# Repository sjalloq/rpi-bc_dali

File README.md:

# rpi-bc_dali
A Dali expander board for the [Phoenix RPI-BC](https://www.phoenixcontact.com/online/portal/gb/pxc/product_list_pages/!ut/p/z1/xVRdb9sgFP0te_AjBscUk72lUZWoq6V13daYF4svO7QxUIfEzb8f3ipVm9ZEUxWNB7hI5557zxEXyOAKMsv3puXBOMs38V4xUtPJp_lygbOSXt1M0G1Z3izxl6zIZgh-hwwyL42CVUNy3WCFAZ5iATClHAhFCWikmnB8UVCJ8xEtbfBhDatWaJugQYsEddzE0PdO7WTYJmhjtqH2vNUxVnqvN8532ob60YS69wYIWXuAMpBNxh0VCeIFVWQqc1Ag0gCMCAdTRXKAeKMKnskpQgLeH1WzwJAdF_srH72xIuBEfhXzizcBtxje740e4Dfr-i6af_eP3i5PViDvrHCC_uKs9OS89OV5zSmLs9Jfvbf761OPN34F5uHpic3iBDsb9HOAq_8xwuxoo-MQ_wQcmdI7bevFZf15NV9cjrqN6NJBdilK_bNMXyTUrwJG6TMrctpC1utG97pPd338HNch-O3HBEULhiFtnWs3OpUu3T0m6G9Ja7eNpv2Jhb7raH4woLreD8PXppsL-vtxyNEDZuIwzD78AHHaYK8!/?q=rpi-bc&uri=pxc-search%3Awebsite&library=gben) case.

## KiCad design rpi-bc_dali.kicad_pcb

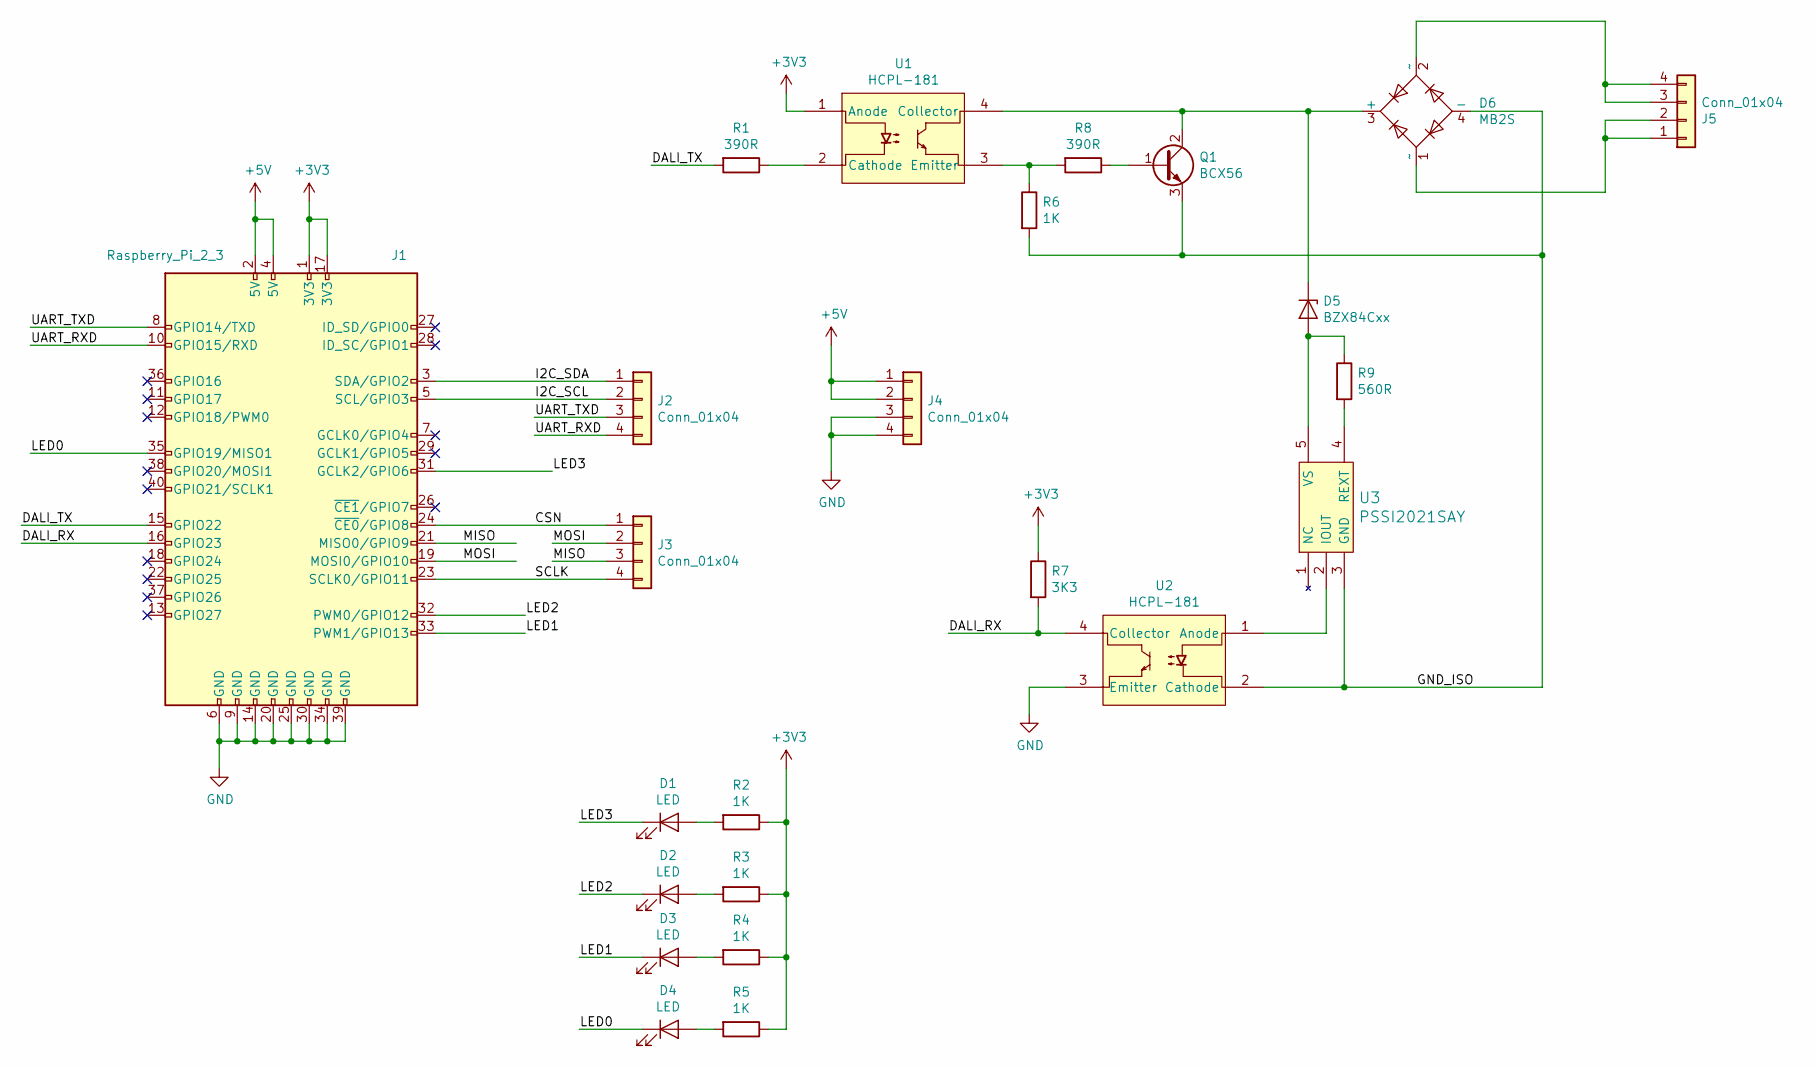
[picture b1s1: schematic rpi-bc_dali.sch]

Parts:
D1, D2, D3, D4: LED; LED_0603_1608Metric_Pad1.05x0.95mm_HandSolder
D5: BZX84Cxx; D_SOT-23_ANK
D6: MB2S; TO-269AA
J1: Raspberry_Pi_2_3; PinSocket_2x20_P2.54mm_Vertical
J2, J3, J4, J5: Conn_01x04; TerminalBlock_Phoenix_PTSM-0,5-4-HH-2,5-THR_1x04_P2.50mm_Ho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
Q1: BCX56; SOT-89-3
R1, R8: 390R; R_0603_1608Metric_Pad1.05x0.95mm_HandSolder
R2, R3, R4, R5, R6: 1K; R_0603_1608Metric_Pad1.05x0.95mm_HandSolder
R7: 3K3; R_0603_1608Metric_Pad1.05x0.95mm_HandSolder
R9: 560R; R_0603_1608Metric_Pad1.05x0.95mm_HandSolder
U1, U2: HCPL-181; SO-4_4.4x3.6mm_P2.54mm
U3: PSSI2021SAY; SOT-353_SC-70-5_Handsoldering

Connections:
+3V3: J1.1 (3V3), J1.17 (3V3), R2.1, R3.1, R4.1, R5.1, R7.1, U1.1 (Anode)
+5V: J1.2 (5V), J1.4 (5V), J4.1, J4.2
/CSN: J1.24 (~CE0~/GPIO8), J3.1
/DALI_RX: J1.16 (GPIO23), R7.2, U2.4 (Collector)
/DALI_TX: J1.15 (GPIO22), R1.2
/GND_ISO: D6.4 (-), Q1.3 (E), R6.2, U2.2 (Cathode), U3.3 (GND)
/I2C_SCL: J1.5 (SCL/GPIO3), J2.2
/I2C_SDA: J1.3 (SDA/GPIO2), J2.1
/LED0: D4.1 (K), J1.35 (GPIO19/MISO1)
/LED1: D3.1 (K), J1.33 (PWM1/GPIO13)
/LED2: D2.1 (K), J1.32 (PWM0/GPIO12)
/LED3: D1.1 (K), J1.31 (GCLK2/GPIO6)
/MISO: J1.21 (MISO0/GPIO9), J3.3
/MOSI: J1.19 (MOSI0/GPIO10), J3.2
/SCLK: J1.23 (SCLK0/GPIO11), J3.4
/UART_RXD: J1.10 (GPIO15/RXD), J2.4
/UART_TXD: J1.8 (GPIO14/TXD), J2.3
GND: J1.6 (GND), J1.9 (GND), J1.14 (GND), J1.20 (GND), J1.25 (GND), J1.30 (GND), J1.34 (GND), J1.39 (GND), J4.3, J4.4, U2.3 (Emitter)
unnamed: D1.2 (A), R2.2
unnamed: D2.2 (A), R3.2
unnamed: D3.2 (A), R4.2
unnamed: D4.2 (A), R5.2
unnamed: D5.1 (K), D6.3 (+), Q1.2 (C), U1.4 (Collector)
unnamed: D5.2 (A), R9.1, U3.5 (VS)
unnamed: D6.1 (~~), J5.1, J5.2
unnamed: D6.2 (~~), J5.3, J5.4
unnamed: Q1.1 (B), R8.1
unnamed: R1.1, U1.2 (Cathode)
unnamed: R6.1, R8.2, U1.3 (Emitter)
unnamed: R9.2, U3.4 (REXT)
unnamed: U2.1 (Anode), U3.2 (IOUT)

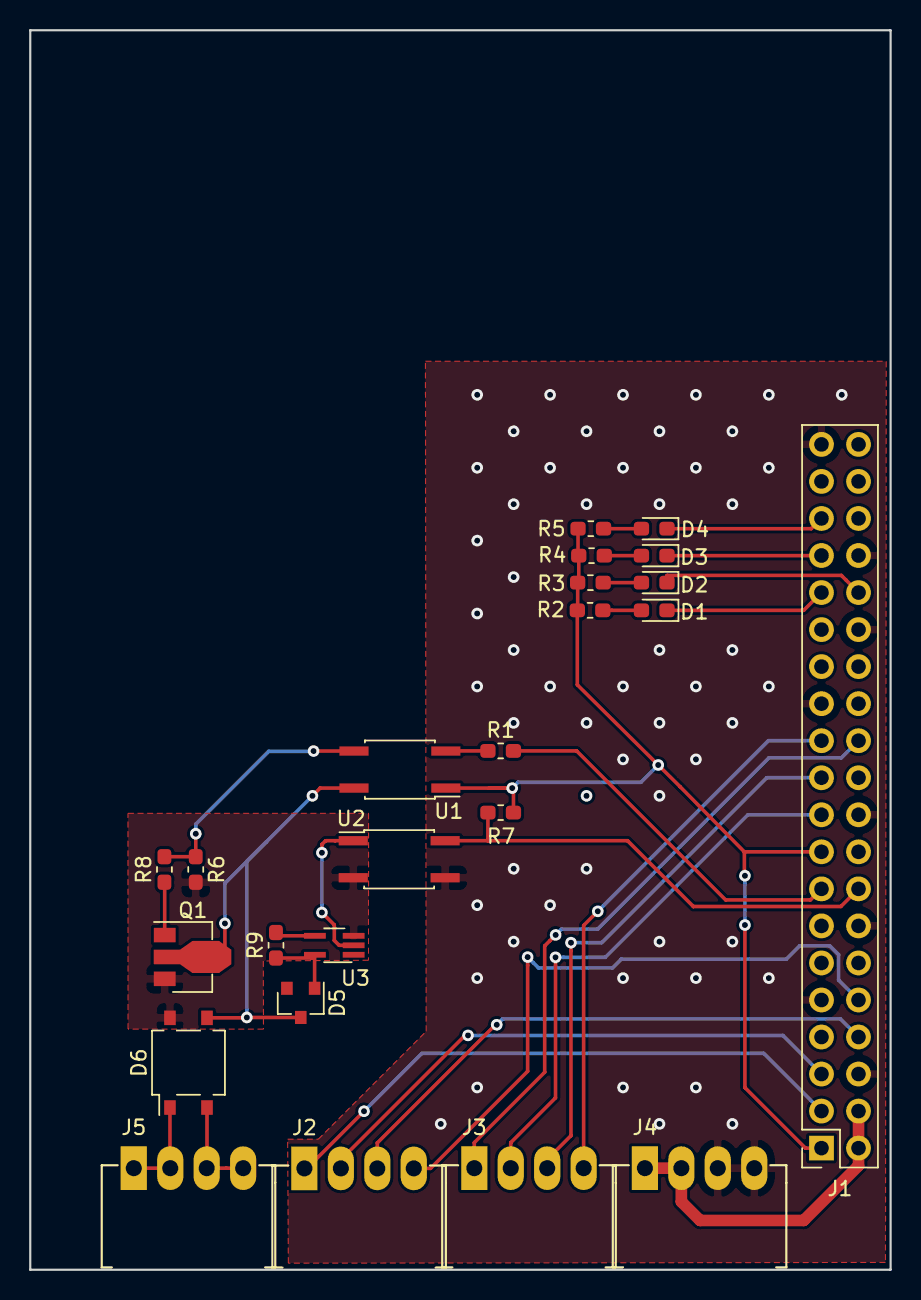
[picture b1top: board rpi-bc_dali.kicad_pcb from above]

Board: 2 copper layers, 59.0 x 85.0 mm, 24 parts (0 on the bottom side), 31 nets.

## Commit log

2019-10-12 master : initial commit
    - Created project from RPI-BC template.
2019-10-12 master : adding license
2019-10-12 master : schematic update
    - first pass schematic.
    - annotated.
2019-10-12 master : first pass at layout
    - minor adjustments to schematic for trace flow
    - all nets routed and polygon's poured.
2020-05-31 master: updates to layout
    - fixed placement bug in GPIO connector.
    - re-routed all nets.
